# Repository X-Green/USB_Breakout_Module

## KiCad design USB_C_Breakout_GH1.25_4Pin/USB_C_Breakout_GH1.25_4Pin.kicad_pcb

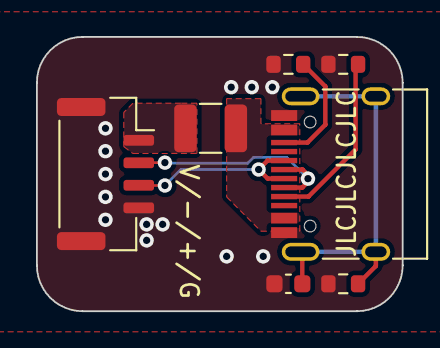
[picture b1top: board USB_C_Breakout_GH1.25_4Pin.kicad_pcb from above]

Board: 2 copper layers, 20.3 x 15.2 mm, 7 parts (0 on the bottom side), 8 nets.

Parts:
C1: 10nF; C_0603_1608Metric
F1: Fuse; Fuse_1210_3225Metric
J1: USB_C_Receptacle_USB2.0; USB_C_Receptacle_HRO_TYPE-C-31-M-12
J2: Conn_01x04_MountingPin; JST_GH_SM04B-GHS-TB_1x04-1MP_P1.25mm_Horizontal
R1, R2: 5.1k; R_0603_1608Metric
R3: 1M; R_0603_1608Metric

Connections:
+5V: F1.1, J2.1
/USB_DM: J1.A7 (D-), J1.B7 (D-), J2.2
/USB_DP: J1.A6 (D+), J1.B6 (D+), J2.3
GND: C1.1, J1.A1 (GND), J1.A12 (GND), J1.B1 (GND), J1.B12 (GND), J2.4, J2.MP (MountPin), R1.1, R2.1, R3.1
unnamed: F1.2, J1.A4 (VBUS), J1.A9 (VBUS), J1.B4 (VBUS), J1.B9 (VBUS)
unnamed: J1.A5 (CC1), R1.2
unnamed: J1.B5 (CC2), R2.2
unnamed: C1.2, J1.S1 (SHIELD), R3.2

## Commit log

2023-03-14 GH1.25 Board Done
2023-03-15 change USB pin sequence to make it more universal
